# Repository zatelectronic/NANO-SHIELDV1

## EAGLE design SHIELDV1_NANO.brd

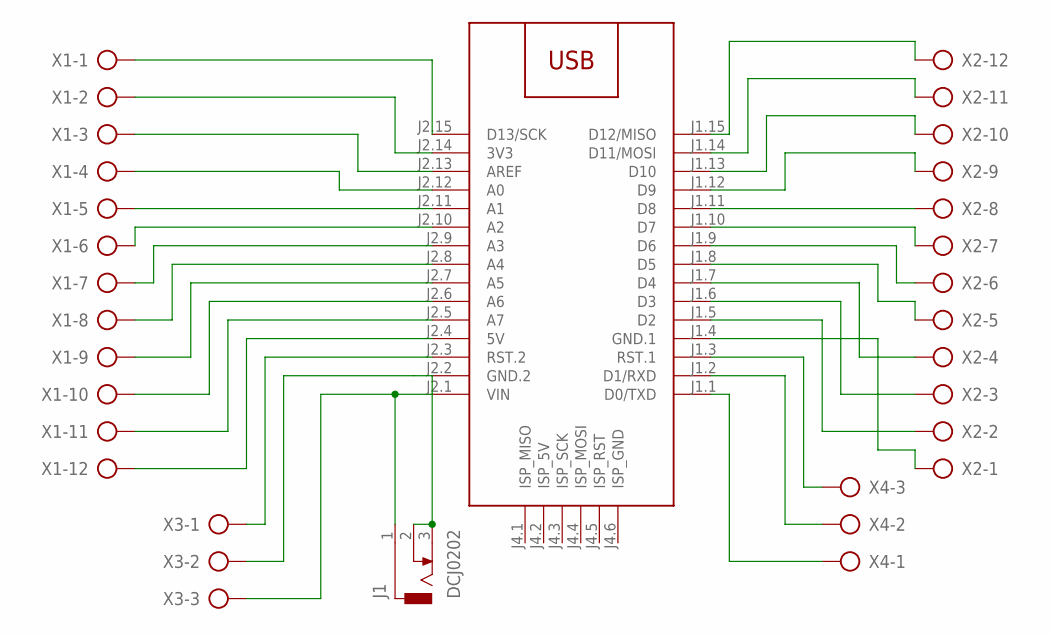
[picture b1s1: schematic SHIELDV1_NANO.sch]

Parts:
J1: DCJ0202
M1: ARDUINO-NANO-3.0#ISP
X1, X2: AK500/12-H
X3, X4: AK500/3

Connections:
unnamed: M1.J2.15 (D13/SCK), X1.1
unnamed: M1.J2.14 (3V3), X1.2
unnamed: M1.J2.13 (AREF), X1.3
unnamed: M1.J2.12 (A0), X1.4
unnamed: M1.J2.11 (A1), X1.5
unnamed: M1.J2.10 (A2), X1.6
unnamed: M1.J2.9 (A3), X1.7
unnamed: M1.J2.8 (A4), X1.8
unnamed: M1.J2.7 (A5), X1.9
unnamed: M1.J2.6 (A6), X1.10
unnamed: M1.J2.5 (A7), X1.11
unnamed: M1.J2.4 (5V), X1.12
unnamed: M1.J1.15 (D12/MISO), X2.12
unnamed: M1.J1.14 (D11/MOSI), X2.11
unnamed: M1.J1.13 (D10), X2.10
unnamed: M1.J1.12 (D9), X2.9
unnamed: M1.J1.11 (D8), X2.8
unnamed: M1.J1.10 (D7), X2.7
unnamed: M1.J1.9 (D6), X2.6
unnamed: M1.J1.8 (D5), X2.5
unnamed: M1.J1.7 (D4), X2.4
unnamed: M1.J1.6 (D3), X2.3
unnamed: M1.J1.5 (D2), X2.2
unnamed: M1.J1.4 (GND.1), X2.1
unnamed: M1.J2.3 (RST.2), X3.1
unnamed: J1.1, M1.J2.1 (VIN), X3.3
unnamed: M1.J1.3 (RST.1), X4.3
unnamed: M1.J1.2 (D1/RXD), X4.2
unnamed: M1.J1.1 (D0/TXD), X4.1
unnamed: J1.2, J1.3, M1.J2.2 (GND.2), X3.2

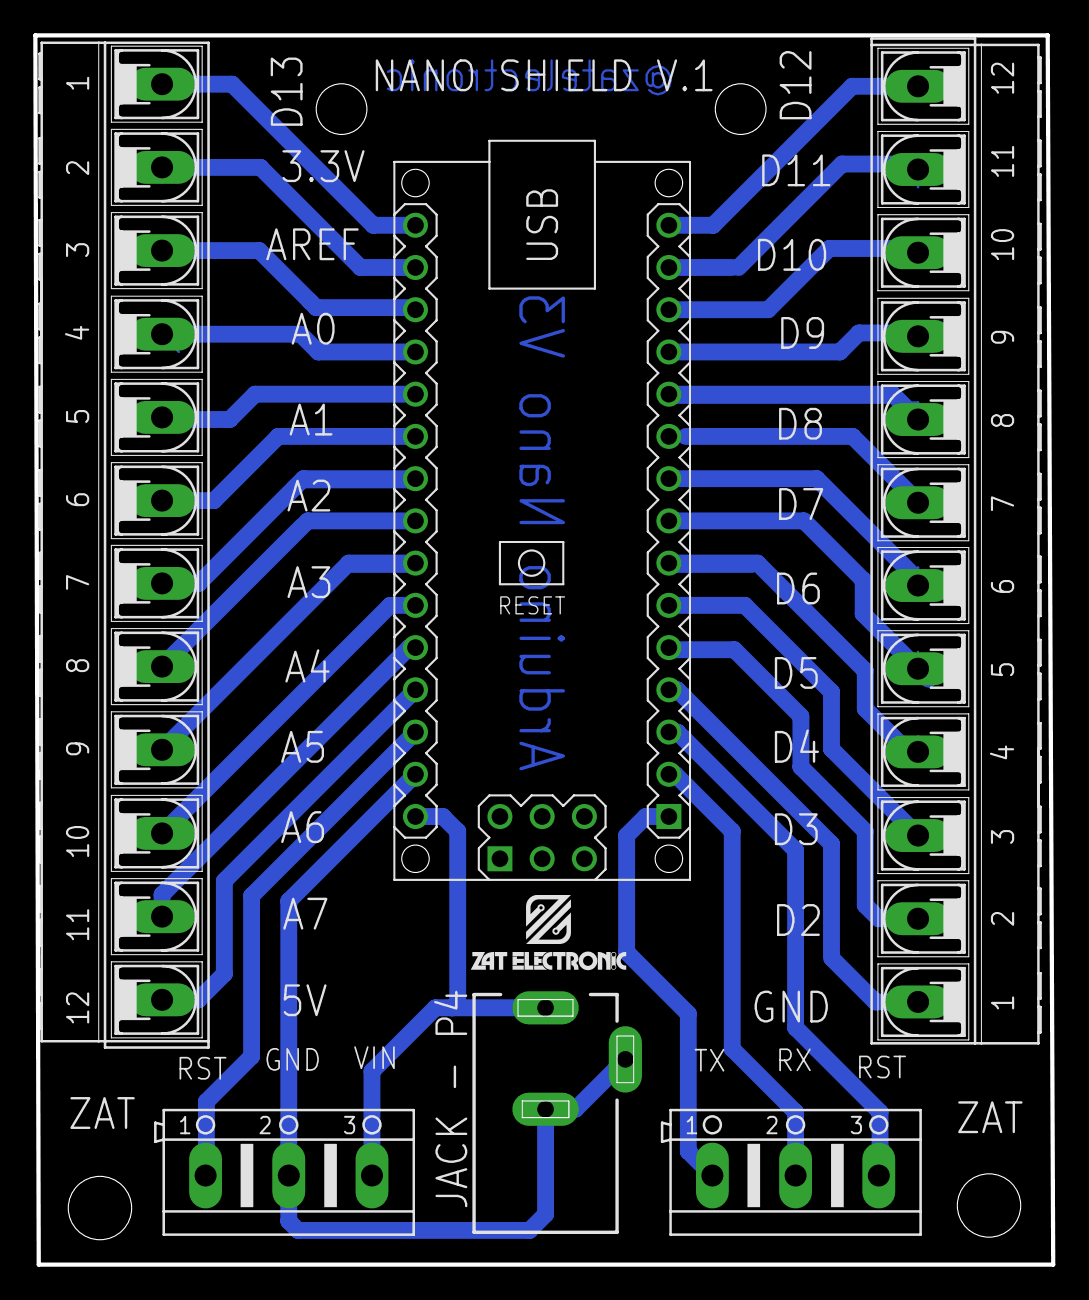
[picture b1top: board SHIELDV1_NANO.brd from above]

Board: 2 copper layers, 61.2 x 73.9 mm, 7 parts (0 on the bottom side), 30 nets.

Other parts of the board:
U$1: LOGO_ESCRITA_PEQUENO

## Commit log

2021-10-23 PRIMEIRO ENVIO
2021-10-25 ATUALIZAÇÃO

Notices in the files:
parts and their libraries:
ARDUINO MODULOS: Released under the Creative Commons Attribution 4.0 International License: http://creativecommons.org/licenses/by/4.0
